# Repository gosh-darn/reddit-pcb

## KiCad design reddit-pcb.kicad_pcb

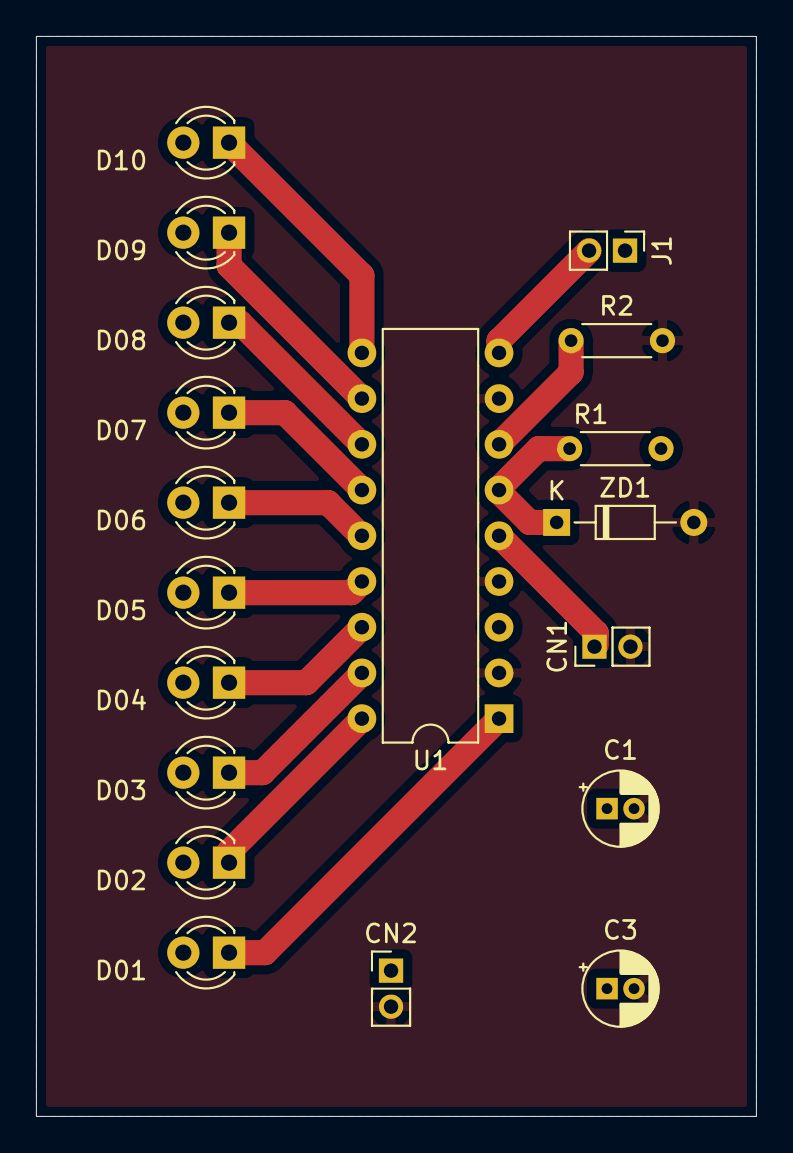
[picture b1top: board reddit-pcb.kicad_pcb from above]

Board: 2 copper layers, 40.0 x 60.0 mm, 19 parts (0 on the bottom side), 16 nets.

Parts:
C1, C3: 0.1 uF; CP_Radial_D4.0mm_P1.50mm
CN1: 0–10VDC; PinHeader_1x02_P2.00mm_Vertical
CN2: Power Supply 12 VDC; PinHeader_1x02_P2.00mm_Vertical
D01, D02, D03, D04, D05, D06, D07, D08, D09, D10: LED; LED_D3.0mm
J1: Jumper; PinHeader_1x02_P2.00mm_Vertical
R1: 1k; R_Axial_DIN0204_L3.6mm_D1.6mm_P5.08mm_Horizontal
R2: 1.2k; R_Axial_DIN0204_L3.6mm_D1.6mm_P5.08mm_Horizontal
U1: LM3914; DIP-18_W7.62mm
ZD1: 10V Zener; D_DO-34_SOD68_P7.62mm_Horizontal

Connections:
GND: C1.2, C3.2, CN1.2, CN2.2, R2.2, U1.2, U1.4, U1.8, ZD1.2
unnamed: C1.1, C3.1, CN2.1, D01.2, D02.2, D03.2, D04.2, D05.2, D06.2, D07.2, D08.2, D09.2, D10.2, J1.1, R1.1, U1.3
unnamed: CN1.1, U1.5
unnamed: D01.1, U1.1
unnamed: D02.1, U1.18
unnamed: D03.1, U1.17
unnamed: D04.1, U1.16
unnamed: D05.1, U1.15
unnamed: D06.1, U1.14
unnamed: D07.1, U1.13
unnamed: D08.1, U1.12
unnamed: D09.1, U1.11
unnamed: D10.1, U1.10
unnamed: J1.2, U1.9
unnamed: R1.2, U1.6, ZD1.1
unnamed: R2.1, U1.7

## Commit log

2021-05-07 kicad files + brd file
